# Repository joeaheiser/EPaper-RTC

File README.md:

# EPaper-RTC
Low power E-Paper display board with real time clock and two capacitive touch buttons.

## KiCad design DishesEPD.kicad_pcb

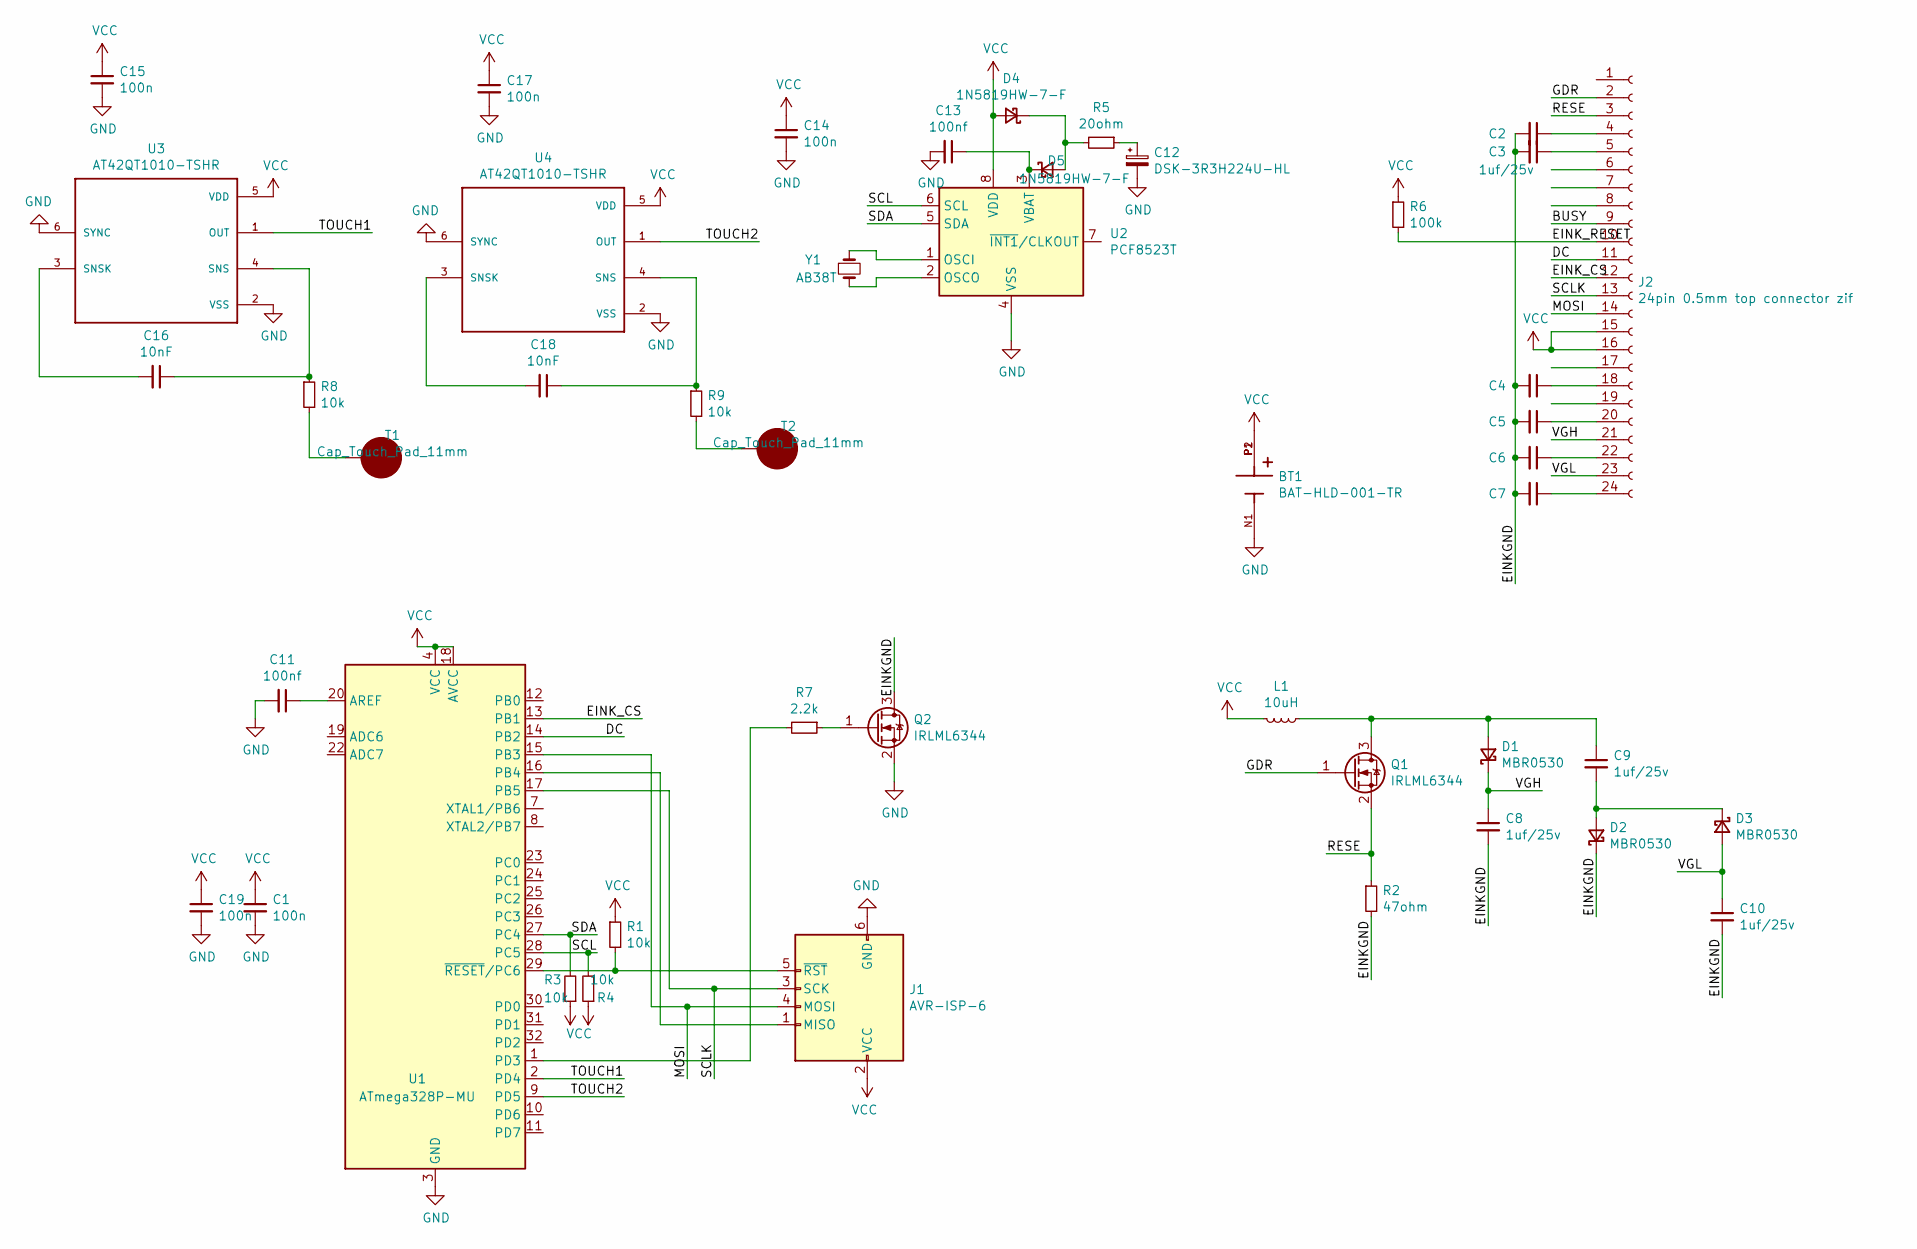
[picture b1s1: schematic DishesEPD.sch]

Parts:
BT1: BAT-HLD-001-TR; BAT_BAT-HLD-001-TR
C1, C14, C15, C17, C19: 100n; C_0805_2012Metric
C2, C8, C9, C10: 1uf/25v; C_0805_2012Metric
C3: csmall; C_0805_2012Metric
C4, C5, C6, C7: C_Small; C_0805_2012Metric
C11, C13: 100nf; C_0805_2012Metric
C12: DSK-3R3H224U-HL; CAP_DSK-3R3H224U-HL
C16, C18: 10nF; C_0805_2012Metric
D1, D2, D3: MBR0530; D_SOD-123
D4, D5: 1N5819HW-7-F; D_SOD-123
J1: AVR-ISP-6; PinHeader_2x03_P2.54mm_Vertical
J2: 24pin 0.5mm top connector zif; TE_2-1734592-4
L1: 10uH; L_0805_2012Metric
Q1, Q2: IRLML6344; SOT-23
R1, R3, R4, R8, R9: 10k; R_0805_2012Metric
R2: 47ohm; R_0805_2012Metric
R5: 20ohm; R_0805_2012Metric
R6: 100k; R_0805_2012Metric
R7: 2.2k; R_0805_2012Metric
T1, T2: Cap_Touch_Pad_11mm; Circle_Pad_11mm
U1: ATmega328P-MU; QFN-32-1EP_5x5mm_P0.5mm_EP3.1x3.1mm
U2: PCF8523T; SOIC-8_3.9x4.9mm_P1.27mm
U3, U4: AT42QT1010-TSHR; SOT95P270X145-6N
Y1: AB38T; XTAL_AB38T-32.768KHZ

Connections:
/BUSY: J2.9
/DC: J2.11, U1.14 (PB2)
/EINKGND: C2.2, C3.2, C4.2, C5.2, C6.2, C7.2, C8.2, C10.2, D2.1 (K), Q2.3 (D), R2.2
/EINK_CS: J2.12, U1.13 (PB1)
/EINK_RESET: J2.10, R6.2
/GDR: J2.2, Q1.1 (G)
/MOSI: J1.4 (MOSI), J2.14, U1.15 (PB3)
/RESE: J2.3, Q1.2 (S), R2.1
/SCL: R4.2, U1.28 (PC5), U2.6 (SCL)
/SCLK: J1.3 (SCK), J2.13, U1.17 (PB5)
/SDA: R3.2, U1.27 (PC4), U2.5 (SDA)
/TOUCH1: U1.2 (PD4), U3.1 (OUT)
/TOUCH2: U1.9 (PD5), U4.1 (OUT)
/VGH: C8.1, D1.1 (K), J2.21
/VGL: C10.1, D3.2 (A), J2.23
GND: BT1.N1, C1.2, C11.2, C12.2, C13.2, C14.2, C15.2, C17.2, C19.2, J1.6 (GND), Q2.2 (S), U1.3 (GND), U1.5 (GND), U1.21 (GND), U1.33 (GND), U2.4 (VSS), U3.2 (VSS), U3.6 (SYNC), U4.2 (VSS), U4.6 (SYNC)
unnamed: C2.1, J2.4
unnamed: C3.1, J2.5
unnamed: C4.1, J2.18
unnamed: C5.1, J2.20
unnamed: C6.1, J2.22
unnamed: C7.1, J2.24
unnamed: C9.1, D1.2 (A), L1.1, Q1.3 (D)
unnamed: C9.2, D2.2 (A), D3.1 (K)
unnamed: C11.1, U1.20 (AREF)
unnamed: C12.1, R5.1
unnamed: C13.1, D5.1 (K), U2.3 (VBAT)
unnamed: C16.1, R8.1, U3.4 (SNS)
unnamed: C16.2, U3.3 (SNSK)
unnamed: C18.1, R9.1, U4.4 (SNS)
unnamed: C18.2, U4.3 (SNSK)
unnamed: D4.1 (K), D5.2 (A), R5.2
unnamed: J1.1 (MISO), U1.16 (PB4)
unnamed: J1.5 (~RST), R1.2, U1.29 (~RESET~/PC6)
unnamed: Q2.1 (G), R7.1
unnamed: R7.2, U1.1 (PD3)
unnamed: R8.2, T1.1, T1.~
unnamed: R9.2, T2.1, T2.~
unnamed: U2.1 (OSCI), Y1.1
unnamed: U2.2 (OSCO), Y1.2
VCC: BT1.P1, BT1.P2, C1.1, C14.1, C15.1, C17.1, C19.1, D4.2 (A), J1.2 (VCC), J2.15, J2.16, L1.2, R1.1, R3.1, R4.1, R6.1, U1.4 (VCC), U1.6 (VCC), U1.18 (AVCC), U2.8 (VDD), U3.5 (VDD), U4.5 (VDD)

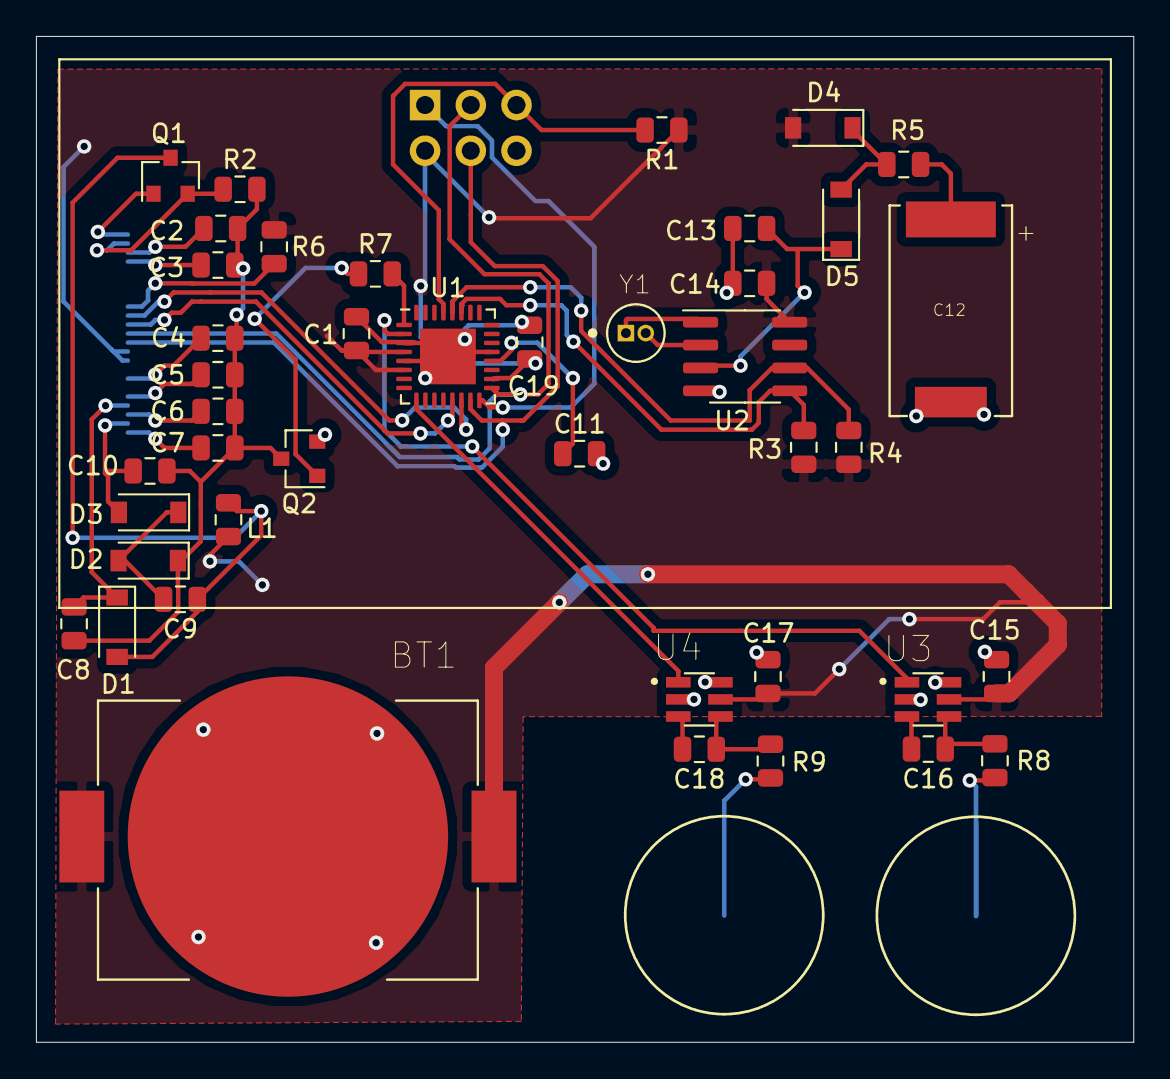
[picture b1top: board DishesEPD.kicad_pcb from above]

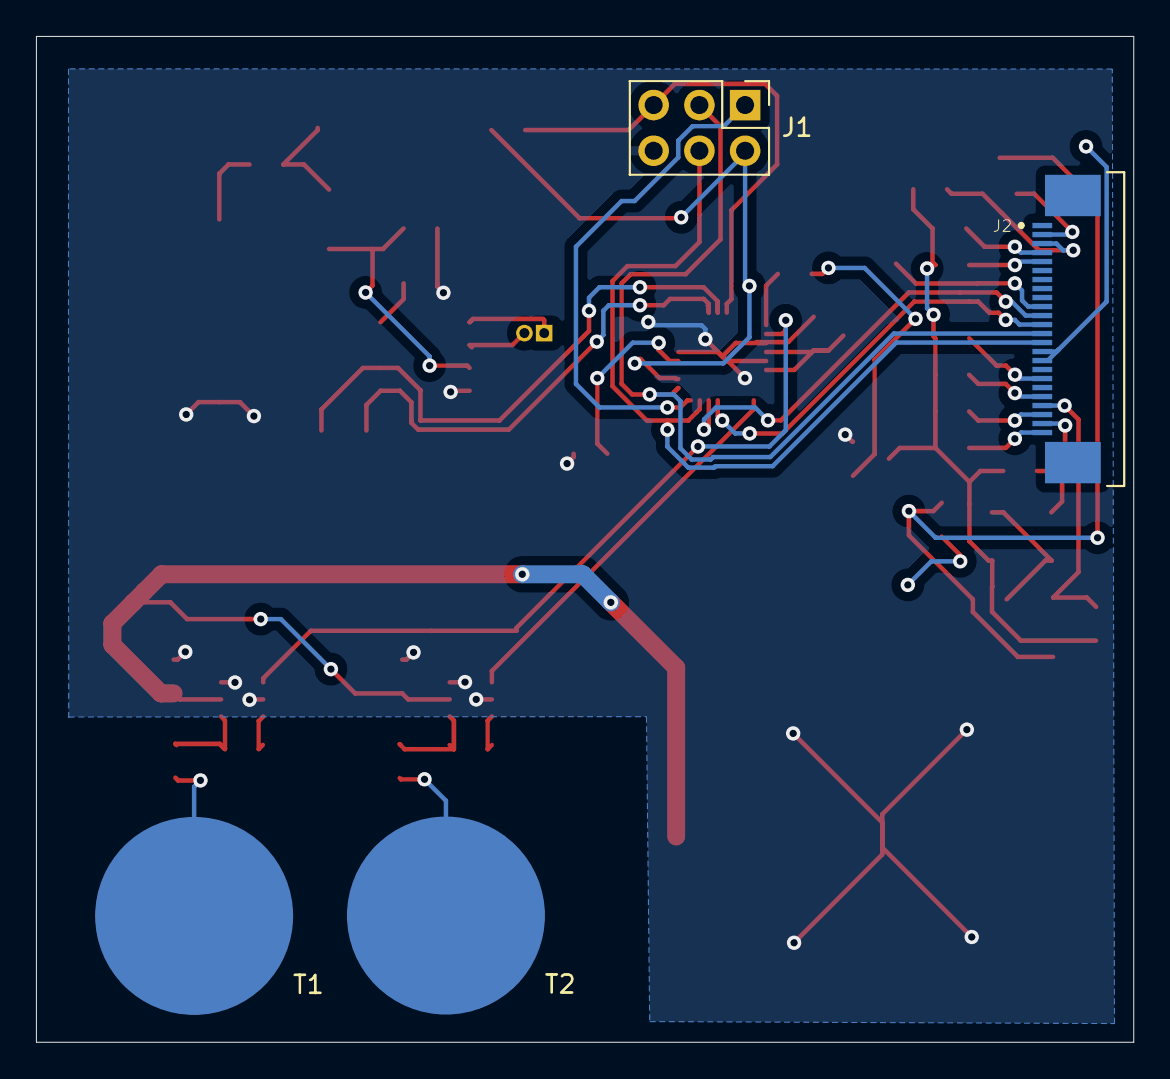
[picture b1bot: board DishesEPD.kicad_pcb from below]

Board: 2 copper layers, 61.0 x 55.9 mm, 46 parts (4 on the bottom side), 40 nets.

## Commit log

2020-10-08 Added schematic and PCB files
2020-10-08 Schematic PDF
